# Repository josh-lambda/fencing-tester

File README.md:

# Fencing Tester

Fencing Tester is a tool for testing and analysing basic fencing equipment. It is intended for situations where you may not have access to a full piste setup to test equipment during repair or when you are tired of manually jabbing a weapon button a hundred times while trying to find which part of a reel/cable set decided to break this time.

It aims to provide basic troubleshooting functionality including:

- Weapon readout for Eppe, Foil & Sabre
- Body wire resistance testing for Eppe, Foil, & Sabre
- Test signal generator for troubleshooting pistes

## Images

### Why did I make this?

I created this project due to an interest in the electrical signaling protocols used in fencing, and fascination with the reliable and intricate mechanisms that make modern blades work. This spiraled into creating a multi-function testing device with signal generation, weapon readout, and wire checking for fun.

## BOM

See BOM.csv for full details

|CATEGORY|ITEM|QUANTITY|
|-------|----|---------|
|COMPONENTS|G6K-2P-Y 5V|6|
||1N4148|5|
||BC547|6|
||10uF Capacitors|2|
||0.1uF/100nF|2|
||1nF Capacitors|1|
||10k Resistor|6|
||510 Resistor|5|
||1 Resistor|3|
||5.1k Resistor|1|
||1M Resistor|1|
||Display 128x128 I2C|1|
||AMS1117-3.3|1|
||Banana Plugs|9|
||3mm Plug|1|
||USB-C Connector|1|
||Pin Headers Female|4|
||Push Button|1|
||2P Switch|1|
||3P Switch|1|
||ESP32-C6-WROOM-1U|1|
|HARDWARE|M4x20 Socket Head|4|
||M2x10 Socket head|4|
|MATERIALS|PLA 1kg|1|
||3mm Sheet|1|

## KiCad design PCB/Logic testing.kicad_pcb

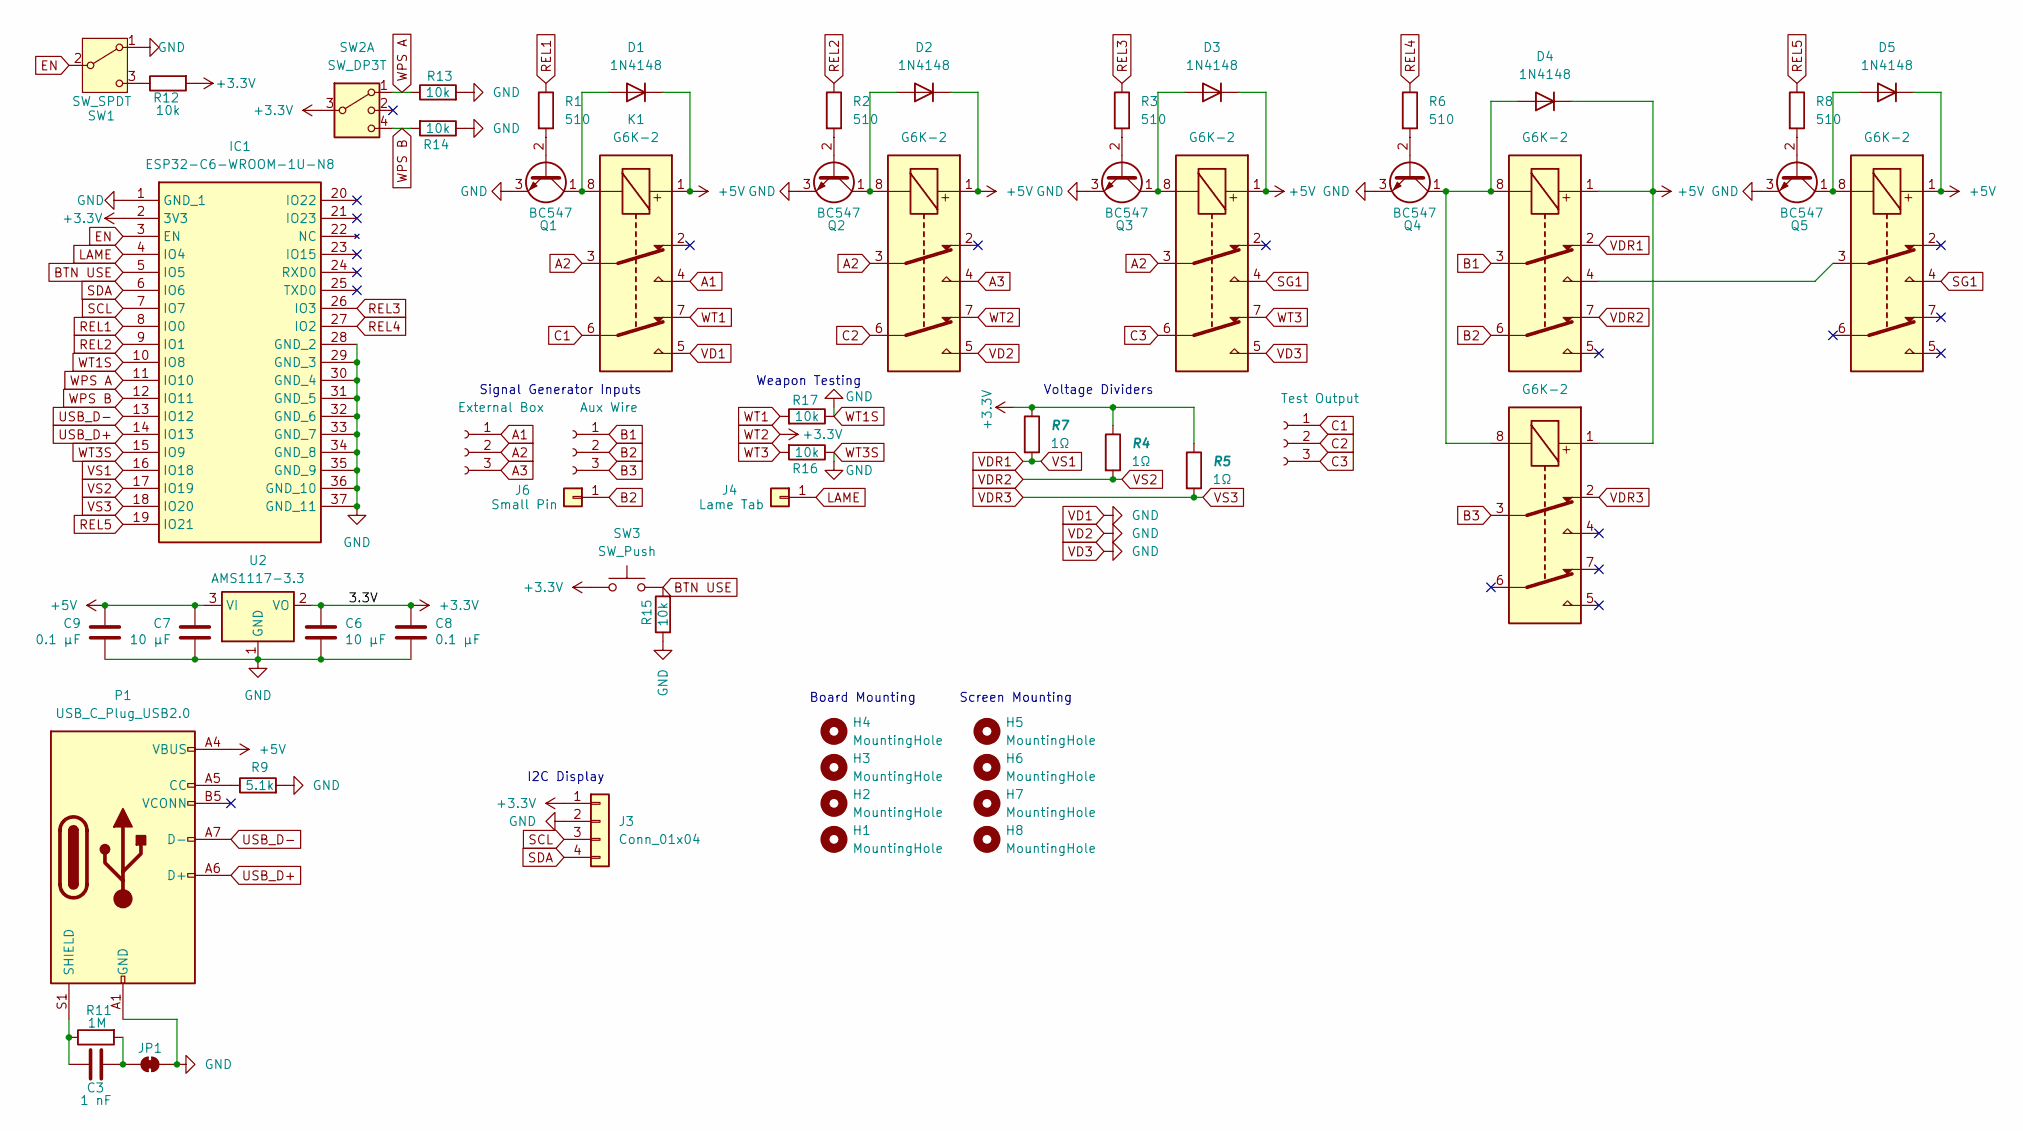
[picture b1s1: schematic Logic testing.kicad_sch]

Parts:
C3: 1 nF; C_0805_2012Metric_Pad1.18x1.45mm_HandSolder
C6, C7: 10 µF; C_0805_2012Metric_Pad1.18x1.45mm_HandSolder
C8, C9: 0.1 µF; C_0805_2012Metric_Pad1.18x1.45mm_HandSolder
D1, D2, D3, D4, D5: 1N4148; D_SOD-123
H1, H2, H3, H4: MountingHole; MountingHole_3.2mm_M3_ISO7380_Pad_TopBottom
H5, H6, H7, H8: MountingHole; MountingHole_2.2mm_M2_DIN965_Pad_TopBottom
IC1: ESP32-C6-WROOM-1U-N8; ESP32C6WROOM1UN8; Manufacturer_Part_Number ESP32-C6-WROOM-1U-N8; Mouser Part Number 356-ESP32C6WROOM1UN8
J1: External Box; Fencing Plug
J2: Aux Wire; Fencing Plug
J3: Conn_01x04; PinSocket_1x04_P2.54mm_Vertical
J4: Lame Tab; SolderWire-0.5sqmm_1x01_D0.9mm_OD2.1mm
J5: Test Output; Fencing Plug
J6: Small Pin; SolderWire-0.5sqmm_1x01_D0.9mm_OD2.1mm
JP1: SolderJumper_2_Closed; SolderJumper-2_P1.3mm_Bridged_RoundedPad1.0x1.5mm
K1, K2, K3, K4, K5, K6: G6K-2; Relay_DPDT_Omron_G6K-2F-Y
P1: USB_C_Plug_USB2.0; USB_C_Receptacle_GCT_USB4085
Q1, Q2, Q3, Q4, Q5: BC547; TO-92_Inline
R1, R2, R3, R6, R8: 510; R_1206_3216Metric_Pad1.30x1.75mm_HandSolder_Text
R4, R5, R7: 1Ω; R_1206_3216Metric_Pad1.30x1.75mm_HandSolder_Text
R9: 5.1k; R_1206_3216Metric_Pad1.30x1.75mm_HandSolder_Text
R11: 1M; R_1206_3216Metric_Pad1.30x1.75mm_HandSolder_Text
R12, R13, R14, R15, R16, R17: 10k; R_1206_3216Metric_Pad1.30x1.75mm_HandSolder_Text
SW1: SW_SPDT; SW_SPDT_CK_JS102011SAQN
SW2: SW_DP3T; SW_SP3T_PCM13
SW3: SW_Push; SW_PUSH_6mm_H13mm
U2: AMS1117-3.3; SOT-223

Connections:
+5V: C7.1, C9.1, D1.1 (K), D2.1 (K), D3.1 (K), D4.1 (K), D5.1 (K), K1.1, K2.1, K3.1, K4.1, K5.1, K6.1, P1.A4 (VBUS), P1.A9 (VBUS), P1.B4 (VBUS), P1.B9 (VBUS), U2.3 (VI)
A1: J1.1, K1.4
A2: J1.2, K1.3, K2.3, K3.3
A3: J1.3, K2.4
B1: J2.1, K4.3
B2: J2.2, J6.1, K4.6
B3: J2.3, K5.3
BTN USE: IC1.5 (IO5), R15.2, SW3.2
C1: J5.1, K1.6
C2: J5.2, K2.6
C3: J5.3, K3.6
EN: IC1.3 (EN), SW1.2 (B)
LAME: IC1.4 (IO4), J4.1
unnamed: D1.2 (A), K1.8, Q1.1 (C)
unnamed: D2.2 (A), K2.8, Q2.1 (C)
unnamed: D3.2 (A), K3.8, Q3.1 (C)
unnamed: D4.2 (A), K4.8, K5.8, Q4.1 (C)
unnamed: D5.2 (A), K6.8, Q5.1 (C)
unnamed: C3.2, JP1.1 (A), R11.2
unnamed: K4.4, K6.3
unnamed: P1.A5 (CC), R9.1
unnamed: C3.1, P1.S1 (SHIELD), R11.1
unnamed: Q1.2 (B), R1.2
unnamed: Q2.2 (B), R2.2
unnamed: Q3.2 (B), R3.2
unnamed: Q4.2 (B), R6.2
unnamed: Q5.2 (B), R8.2
unnamed: R12.1, SW1.3 (C)
REL1: IC1.8 (IO0), R1.1
REL2: IC1.9 (IO1), R2.1
REL3: IC1.26 (IO3), R3.1
REL4: IC1.27 (IO2), R6.1
REL5: IC1.19 (IO21), R8.1
SCL: IC1.7 (IO7), J3.3
SDA: IC1.6 (IO6), J3.4
SG1: K3.4, K6.4
USB_D+: IC1.14 (IO13), P1.A6 (D+)
USB_D-: IC1.13 (IO12), P1.A7 (D-)
VD1: C6.2, C7.2, C8.2, C9.2, IC1.1 (GND_1), IC1.10 (IO8), IC1.15 (IO9), IC1.28 (GND_2), IC1.29 (GND_3), IC1.30 (GND_4), IC1.31 (GND_5), IC1.32 (GND_6), IC1.33 (GND_7), IC1.34 (GND_8), IC1.35 (GND_9), IC1.36 (GND_10), IC1.37 (GND_11), J3.2, JP1.2 (B), K1.5, K2.5, K3.5, P1.A1 (GND), P1.A12 (GND), P1.B1 (GND), P1.B12 (GND), Q1.3 (E), Q2.3 (E), Q3.3 (E), Q4.3 (E), Q5.3 (E), R9.2, R13.2, R14.1, R15.1, R16.1, R17.1, SW1.1 (A), U2.1 (GND)
VDR1: IC1.16 (IO18), K4.2, R7.2
VDR2: IC1.17 (IO19), K4.7, R4.2
VDR3: IC1.18 (IO20), K5.2, R5.2
WPS A: IC1.11 (IO10), R13.1, SW2.1
WPS B: IC1.12 (IO11), R14.2, SW2.4
WT1: K1.7, R17.2
WT2: C6.1, C8.1, IC1.2 (3V3), J3.1, K2.7, R4.1, R5.1, R7.1, R12.2, SW2.3, SW3.1, U2.2 (VO)
WT3: K3.7, R16.2

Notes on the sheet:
Weapon Testing
Screen Mounting
Board Mounting
I2C Display
Voltage Dividers
Signal Generator Inputs

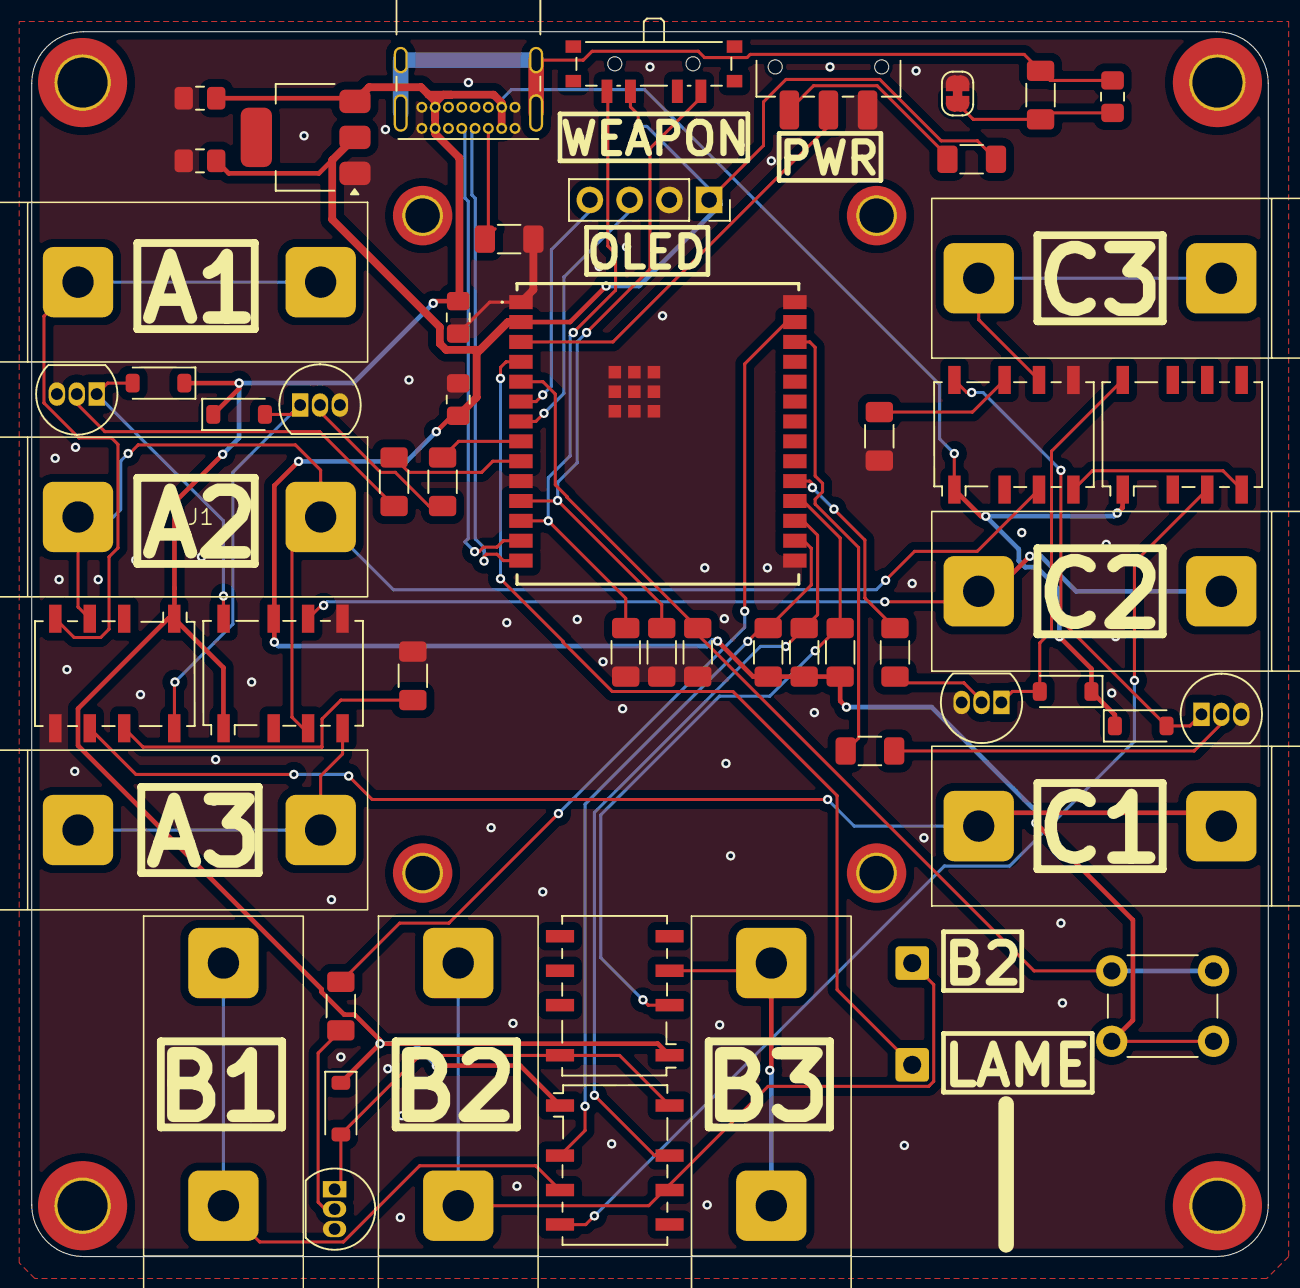
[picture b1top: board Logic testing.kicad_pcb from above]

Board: 2 copper layers, 79.0 x 78.2 mm, 58 parts (0 on the bottom side), 47 nets.

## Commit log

2025-05-31 Add first Journal entry
2025-06-01 Add pinout image; Work on journal
2025-06-01 Add hit detection to journal
2025-06-01 add implementation of hit detection to journal
2025-06-01 Implementation of resistance checking to journal
2025-06-01 Do hardware + journal for test signal relay; Create schematic for relays; Move images to folder
2025-06-01 Update JOURNAL.md - Change image spacing
2025-06-01 Begin sourcing parts and working on BOM
2025-06-03 Add voltage divider schematics and journal entry;
2025-06-03 Update BOM for dividers
2025-06-03 Add weapon tester & change layout
2025-06-09 Update schematic and BOM
2025-06-16 Worked on microcontroller; Accidentally deleted info from previous journal update;
2025-07-01 Add usb, es32 c6, and voltage regulator
2025-07-01 Kicad
2025-07-02 Transitioned relays to 5V; Fixed USB port shield; Added buttons, switches;
2025-07-02 Work on footprints, suppliers, BOM
2025-07-06 Journal; BOM changes; PCB changes
2025-07-07 Worked on new power; Worked on display; Replaces ESP controller; Restructured schematic; Worked on PCB layout; Did journal
2025-07-09 Worked on connectors, PCB layout, created footprints, component CAD, journal
2025-07-09 Worked on layout and footprints
2025-07-14 Work from 14th
2025-07-16 Finished PCB
2025-07-17 Finished PCB; Updated USB-C connector; Stated on CAD
2025-07-18 More final changes to PCB; Added cut outs & 3mm to CAD; Started programming
2025-07-19 worked on code; journaled; realised issues
2025-07-20 Worked on issues
2025-07-21 Updated journal from yesterday
2025-07-21 Worked on PCB; worked on Code; Worked on journal
2025-07-22 Made last changes to CAD, PCB, & journal. Ready for submission
2025-07-22 Forgot to include pcb in bom...
2025-07-25 Journal; Changed file locations; Part revisions; Exported production files
2025-07-25 forgot to save journal before pushing :(
